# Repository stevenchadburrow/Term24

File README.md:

# Term24
VGA Terminal/Graphics Module using a PIC24<br>

This module is designed to output an 80x24 Terminal to a VGA display.  It accepts standard ANSI escape codes and includes customized escape codes for switching modes and changing internal memory.  It also has the capability of displaying 128x128 pixels at 128 colors, either double-buffered, layered, or with scrolling.  It has built in buttons to double as a gamepad.<br>

It can be accessed through four different protocols: UART, PS/2 Keyboard, SPI, or Parallel Input.  It can be used as a shield for the Arduino Uno, or it can be used with any homebrew computer and is easily plugged in to a breadboard.  It also has 'Tetra' as a built-in game!<br>

It uses the PIC24EP512GP202 microcontroller, running at 65 MIPS and containing 512KB of ROM and 48KB of RAM.  The only other IC on-board is the LM1117 voltage regulator.  All components are through-hole for ease of soldering.<br>

<br>
<br>
<br>
<br>
<br>
<br>
<br>
<br>
<br>
<br>
<br>

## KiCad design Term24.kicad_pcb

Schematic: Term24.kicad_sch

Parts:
A1: Arduino_UNO_R3; Arduino_UNO_R3-Revised
C1, C6, C8: C_Polarized_Small_US; CP_Radial_D6.3mm_P2.50mm
C2, C3: C_Polarized_US; CP_Radial_D8.0mm_P3.50mm
C5, C19, C25, C26: C_Small; C_Disc_D3.0mm_W2.0mm_P2.50mm
J1: USB_B; USB_B_Lumberg_2411_02_Horizontal
J2: Conn_01x16; PinSocket_1x16_P2.54mm_Horizontal
J5: Mini-DIN-6; PS2_Din6
J11: VGA DE15; DSUB-15-HD_Socket_Horizontal_P2.29x2.54mm_EdgePinOffset8.35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
J14, J15: Conn_01x06; PinSocket_1x06_P2.54mm_Horizontal
JP1, JP2, JP3, JP4, JP5, JP6, JP7, JP8, JP9, JP10, JP11, JP12, JP13: Jumper_2_Open; SolderJumper-2_P1.3mm_Open_Pad1.0x1.5mm
R2, R9, R14, R16, R17, R18, R19, R20, R28, R29, R30, R31, R32, R33, R34, R35, R36, R37, R38, R39, R40, R41, R42, R43, R44, R45, R46: R_US; R_Axial_DIN0207_L6.3mm_D2.5mm_P10.16mm_Horizontal
RN1: R_Network08_US; R_Array_SIP9
SW3: SW_SPDT; SW_E-Switch_EG1224_SPDT_Angled
SW4, SW5, SW6, SW7, SW8, SW9: SW_Push; SW_PUSH_6mm_H7.3mm
SW10: SW_DIP_x04; SW_DIP_SPSTx04_Slide_9.78x12.34mm_W7.62mm_P2.54mm
SW11: SW_Push; SW_Tactile_SPST_Angled_PTS645Vx83-2LFS
TP1, TP6, TP7, TP8, TP9, TP10, TP11, TP12, TP13, TP14, TP15, TP16, TP17, TP18, TP19, TP20, TP21, TP22, TP23, TP24, TP25, TP26, TP27, TP28, TP29, TP30, TP31, TP32, TP33, TP34, TP35, TP36, TP37, TP38, TP39, TP40, TP41, TP42, TP43, TP44, TP45, TP46, TP47, TP48, TP49, TP50, TP51, TP52, TP53, TP54, TP55, TP56, TP57, TP58, TP59, TP60, TP61, TP62, TP63, TP64, TP65, TP66, TP67, TP68, TP69, TP70, TP71, TP72, TP73, TP74, TP75, TP76, TP77, TP78, TP79, TP80, TP81, TP82, TP83, TP84, TP85, TP86, TP87, TP88, TP89, TP90, TP91, TP92, TP93, TP94, TP95, TP96, TP97, TP98, TP99, TP100, TP101, TP102, TP103, TP104, TP105, TP106, TP107, TP108, TP109, TP110, TP111, TP112, TP113, TP114, TP115, TP116, TP117, TP118, TP119, TP120, TP121, TP122, TP123, TP124, TP125, TP126, TP127, TP128, TP129, TP130, TP131, TP132, TP133, TP134, TP135, TP136, TP137, TP138, TP139, TP140, TP141, TP142, TP143, TP144, TP145, TP146, TP147, TP148: TestPoint; PinHeader_1x01_P2.54mm_Vertical_TestPoint
TP2, TP3, TP4, TP5: TestPoint; ScrewHole-4-40
U1: PIC24EP512GP202-I/SP; DIP-28_W7.62mm_Socket
U5: LM1117T-3.3; TO-223-3-WithPad

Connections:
+3V3: C3.1, C6.1, C19.2, C25.2, J2.12, J14.2, JP13.2 (B), R2.2, U1.13 (VDD), U1.28 (AVDD), U5.2 (VO)
+5V: A1.5 (+5V), C2.1, C5.2, C8.1, C26.2, J2.11, J5.4, RN1.1 (common), SW3.2 (B), U5.3 (VI)
GND: A1.6 (GND), A1.7 (GND), A1.29 (GND), C1.2, C2.2, C3.2, C5.1, C6.2, C8.2, C19.1, C25.1, C26.1, J1.4 (GND), J1.SH (Shield), J2.13, J2.14, J5.3, J11.5, J11.6, J11.7, J11.8, J11.10, J14.3, J15.1, R33.1, R34.1, R36.2, R38.2, R40.2, R42.2, R44.2, R46.2, SW4.2, SW5.2, SW6.2, SW7.2, SW8.2, SW9.2, SW11.2, TP2.1 (1_1), TP3.1 (1_1), TP4.1 (1_1), TP5.1 (1_1), U1.8 (VSS), U1.19 (VSS), U1.27 (AVSS), U5.1 (GND)
ICSP-CLK: J14.5, SW10.3, U1.5 (PGEC3/VREF+/AN3/OA1OUT/RPI33/CTED1/RB1)
ICSP-DAT: J14.4, SW10.4, U1.4 (PGED3/VREF-/AN2/C2IN1-/*SS1/RPI32/CTED2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)
JOY-A: A1.22 (D7), JP12.1 (A), RN1.2 (R1), SW8.1
JOY-B: A1.21 (D6), JP11.1 (A), RN1.3 (R2), SW9.1
JOY-D: A1.19 (D4), JP9.1 (A), RN1.5 (R4), SW5.1
JOY-L: A1.18 (D3), JP8.1 (A), RN1.6 (R5), SW6.1
JOY-R: A1.17 (D2), JP7.1 (A), RN1.7 (R6), SW7.1
JOY-U: A1.20 (D5), JP10.1 (A), RN1.4 (R3), SW4.1
unnamed: R33.2, SW10.6
unnamed: R34.2, SW10.5
PORT-A0-3V3: JP1.2 (B), JP7.2 (B), R35.2, R36.1, U1.2 (AN0/OA2OUT/RA0)
PORT-A0-5V: J2.9, JP1.1 (A), R35.1
PORT-A1-3V3: JP2.2 (B), JP8.2 (B), R37.2, R38.1, U1.3 (AN1/C2IN1+/RA1)
PORT-A1-5V: J2.8, JP2.1 (A), R37.1
PORT-A2-3V3: JP3.2 (B), JP9.2 (B), R39.2, R40.1, U1.9 (OSC1/CLKI/RA2)
PORT-A2-5V: J2.7, JP3.1 (A), R39.1
PORT-A3-3V3: JP4.2 (B), JP10.2 (B), R41.2, R42.1, U1.10 (OSC2/CLKO/RA3)
PORT-A3-5V: J2.6, JP4.1 (A), R41.1
PORT-B2-3V3: JP5.2 (B), JP11.2 (B), R43.2, R44.1, U1.6 (PGEC1/AN4/C1IN1+/RPI34/RB2)
PORT-B2-5V: J2.5, JP5.1 (A), R43.1
PORT-B3-3V3: JP6.2 (B), JP12.2 (B), R45.2, R46.1, U1.7 (PGED1/AN5/C1IN1-/RP35/RB3)
PORT-B3-5V: J2.4, JP6.1 (A), R45.1
POWER: J1.1 (VBUS), SW3.1 (A)
SERIAL-CLK-TX: A1.28 (D13), J2.1, J5.5, J15.5, RN1.9 (R8), SW10.1, U1.15 (PGEC2/ASCL2/RP38/RB6^)
SERIAL-MISO-EX: A1.27 (D12), J2.3, U1.11 (^RP36/RB4)
SERIAL-MOSI-RX: A1.26 (D11), J2.2, J5.1, J15.4, RN1.8 (R7), SW10.2, U1.14 (^PGED2/ASDA2/RP37/RB5)
UNO-3V3: A1.4 (3V3), JP13.1 (A)
UNO-RX: A1.15 (D0/RX), SW10.8
UNO-TX: A1.16 (D1/TX), SW10.7
VCAP: C1.1, U1.20 (VCAP)
VGA-BLUE-A: R19.2, U1.18 (TMS/ASDA1/SDI1/RP41/RB9^)
VGA-BLUE-B: R20.2, U1.17 (TCK/CVREF1O/ASCL1/SDO1/RP40/T4CK/RB8)
VGA-BLUE-OUT: J11.3, R19.1, R20.1, R29.1, R32.1
VGA-GREEN-A: R16.2, U1.22 (TDI/RP43/RB11^)
VGA-GREEN-B: R17.2, U1.21 (TDO/RP42/RB10^)
VGA-GREEN-OUT: J11.2, R16.1, R17.1, R28.1, R31.1
VGA-H-SYNC: J11.13, U1.12 (CVREF20/RP20/T1CK/RA4)
VGA-INTENSITY: R18.2, R28.2, R29.2, U1.25 (RPI46/T3CK/RB14^)
VGA-RED-A: R9.2, U1.24 (RPI45/CTPLS/RB13^)
VGA-RED-B: R14.2, U1.23 (RPI44/RB12^)
VGA-RED-OUT: J11.1, R9.1, R14.1, R18.1, R30.1
VGA-V-SYNC: J11.14, U1.16 (SCK1/RP39/INT0/RB7)
VGA-WHITE: R30.2, R31.2, R32.2, U1.26 (RPI47/T5CK/RB15^)
~MCLR: A1.3 (~RESET), J2.10, J14.1, R2.1, SW11.1, U1.1 (*MCLR)

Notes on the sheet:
1.1K then 2.2K to drop 5V to 3V3
Steven Chad Burrow, July 2026
10K ohms
https://falstad.com/circuit/circuitjs.html?ctz=DwYwlgTgBAZgvAIgIwKgFwM6IAwDpsEECsqYIiSeATAVQOx0DM2AHFQGwCcndqIARoiLZUAB0EIALI1QA3CENQBbTEICmAWiQoAfACgoUYAGUoADwrtGVKDRZQkRRu1utU8BCKiiKqADZgOKhoABaIVAgA9PqGJuaW1rYs9o7OSSzuQd6+UAFZoeFRMUYASvHIknQ2SJzVldVUGbBZAO4eXkoAhmayiIy4MtEGRi3lSPUOtQ5OLjURzchFw8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
RGB-A = 820 ohms RGB-B = 1.5K ohms INT = 560 ohms WHITE = 390 ohms
Term24
All bypass caps are 0.1uF

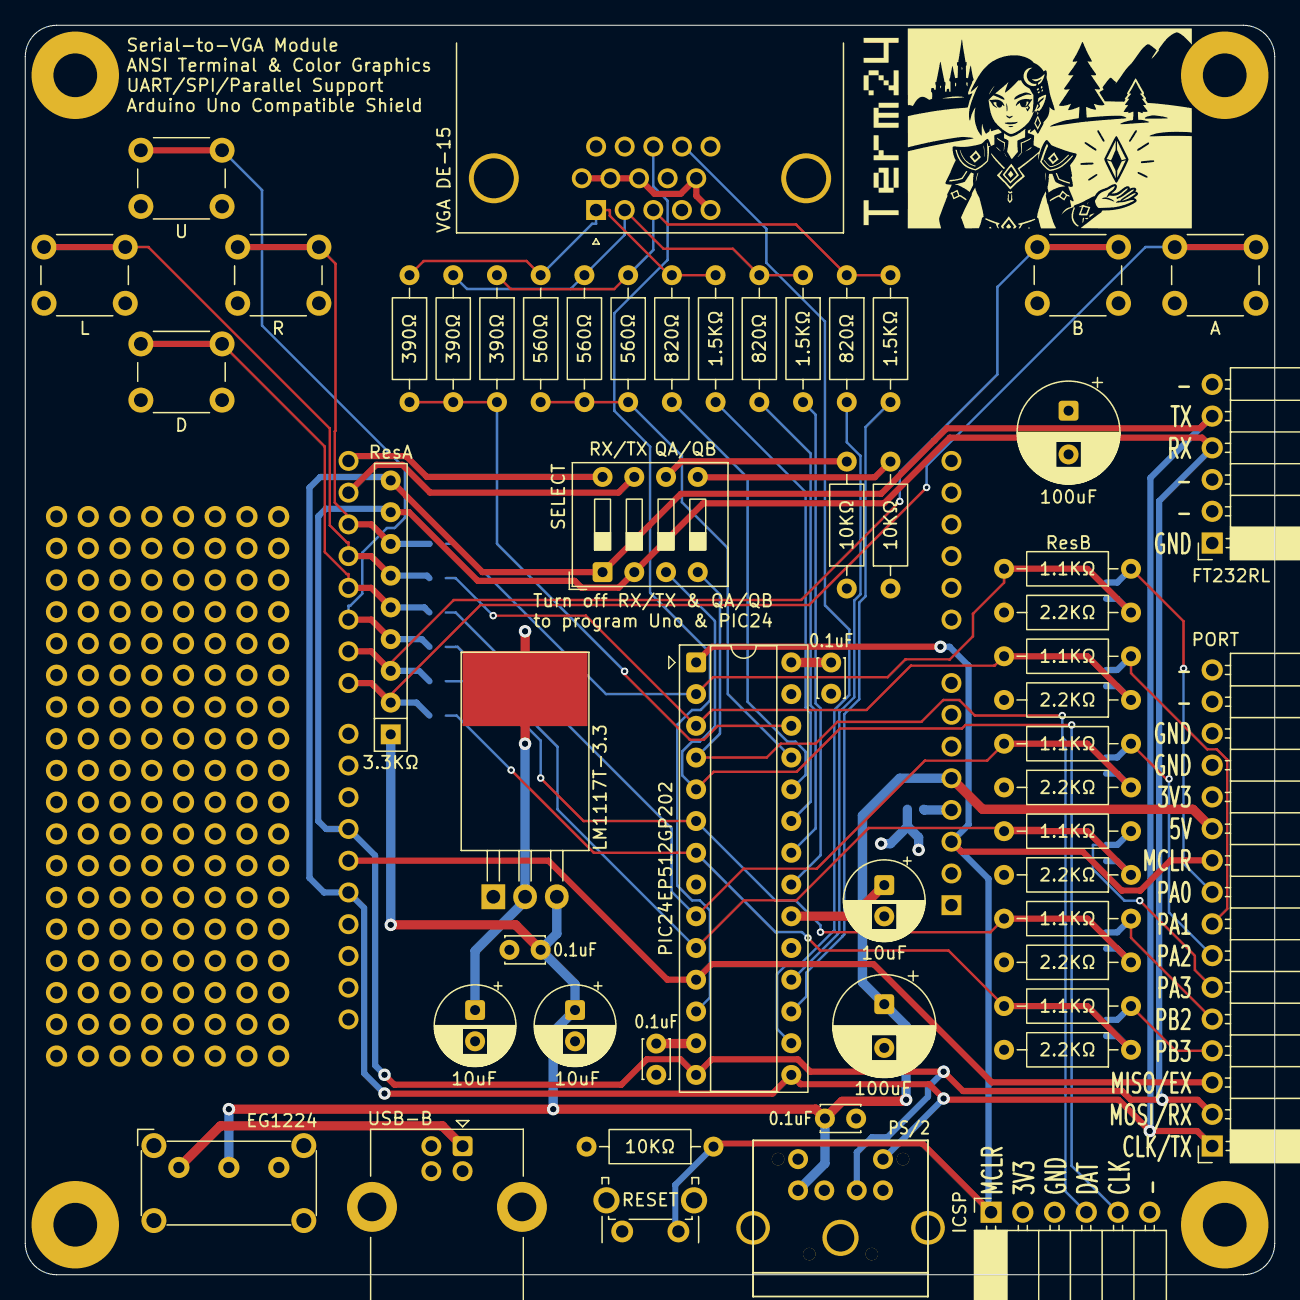
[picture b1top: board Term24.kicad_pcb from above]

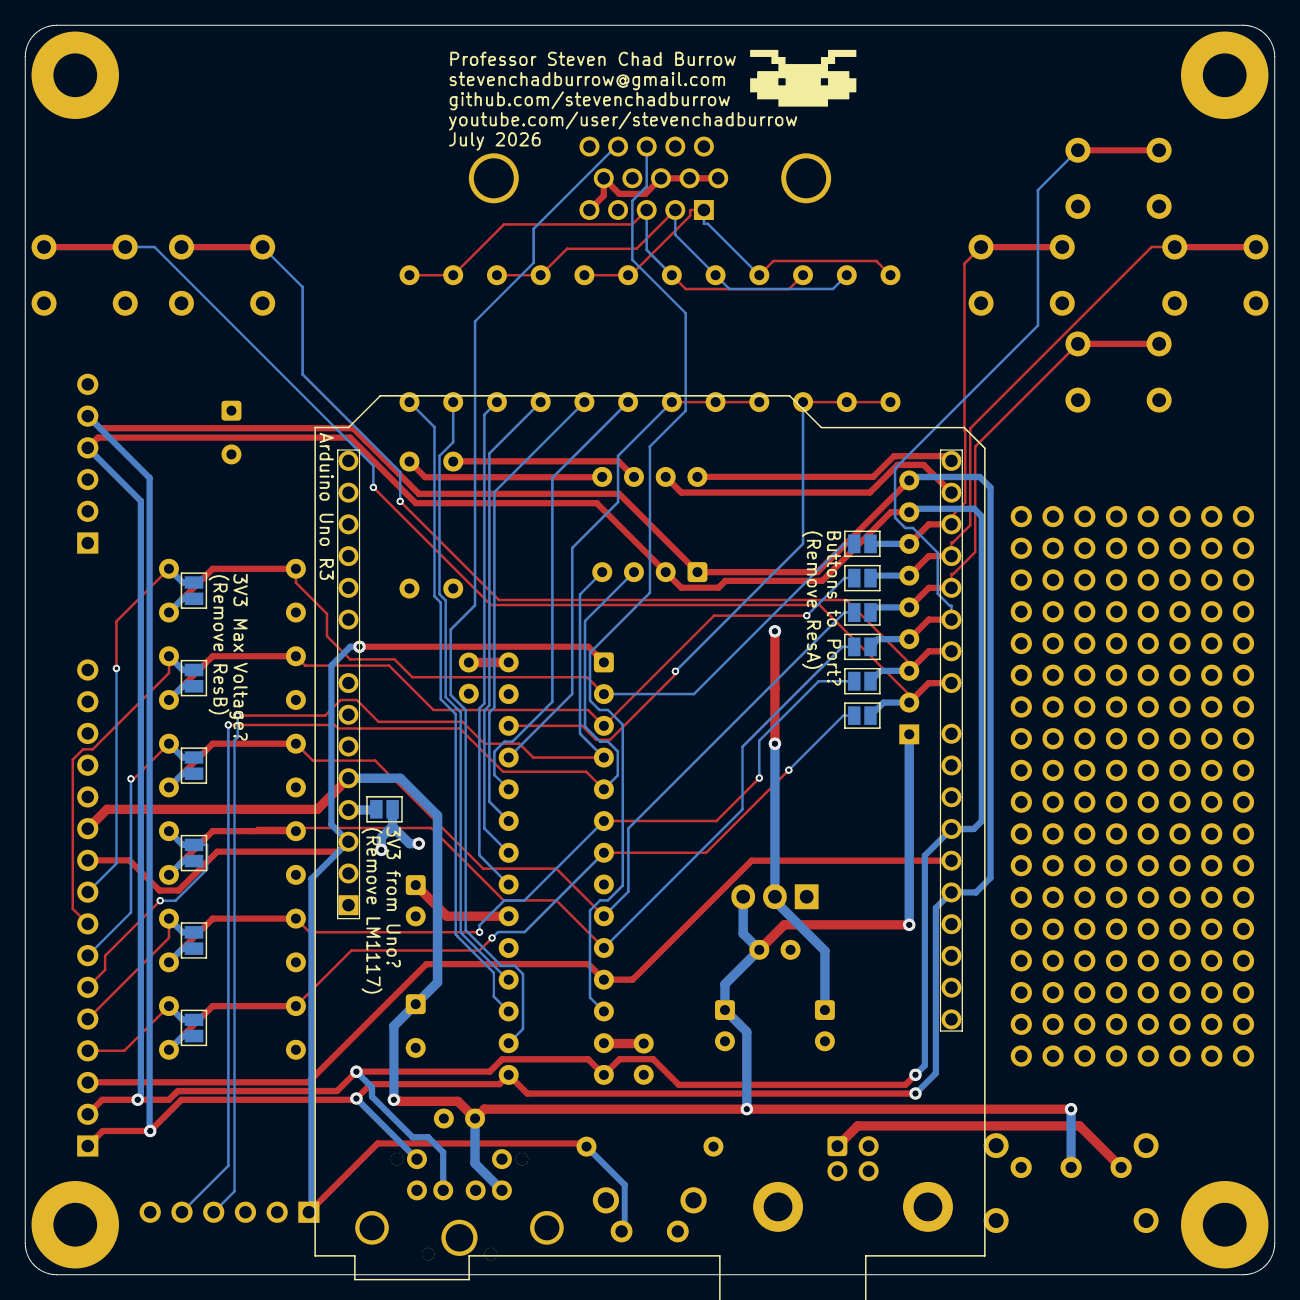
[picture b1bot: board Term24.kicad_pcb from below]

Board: 4 copper layers, 100.0 x 100.0 mm, 219 parts (15 on the bottom side), 47 nets.

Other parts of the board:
G100: LOGO; Title
G101: LOGO; Logo
G102: LOGO; Girl
